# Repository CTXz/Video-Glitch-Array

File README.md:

# Video Glitch Array

Video Glitch Array is a glitch art project in which I attempt to create aesthetics explicitly by manipulating VGA signals in real time trough analog and digital circuits. In a way, Video Glitch Array has become a nice sandbox for me to test and further develop my recently acquired skills in the field of electronics engineering.

## Contents

- [Why VGA](#Why-VGA)
- [Brief summary of how VGA works](#Brief-summary-of-how-VGA-works)
- [Circuits](#Circuits)
- [Open Hardware](#Open-Hardware)
- [Credits](#Credits)
- [Demonstrations](#Demonstrations)

## Why VGA

Quite frankly, the initial reason why I chose to tamper with VGA signals over, say the much more common and within the analog glitch art community preferred composite video signals, is because that is simply what I had available at home. That being said, while VGA certainly has its drawbacks when it comes to glitch art, mostly due to the rather high frequencies of the color signals, it also comes with a variety of advantages.

While the VGA port has practically gone extinct from host peripherals, it is still very common to find a VGA port on most displays, including many released even at the time of writing. Yet I am not aware of many LCD displays and projectors that support composite video. While HDMI and DVI ports are equally common, if not even more common than VGA at this point (with HDMI becoming more and more of a dominant player), those are digital interfaces and as many could imagine, are more clunky and difficult to work with. Another big advantage that VGA offers over composite is the absence of region specific differences. The VGA signal protocol, although a little hidden from the common user, is well established and standardized by now. Oh, and did I mention that VGA comes with its own 5V supply bus which can be used to power your glitch circuits without an external power source?

I could likely be going on forever, but I believe I have already managed to demonstrate that VGA can be an attractive medium for glitch art.

## Brief summary of how VGA works

I could explain how VGA signals work, however due to my brutally honest laziness and lack of competence in explaining things, I will leave you with a few resources which in my opinion do a much better job of explaining VGA than me. Many of the resources below explain VGA as part of a guide to create your own VGA driver, so it is not expected, nor required, that everything is understood.

- [Go Board - VGA Introduction](https://www.nandland.com/goboard/vga-introduction-test-patterns.html) by nandland
- [VGA - the Rest of the Story](http://www.xess.com/blog/vga-the-rest-of-the-story/) by Dave Vandenbout
- [VGA Video Output](http://web.mit.edu/6.111/www/labkit/vga.shtml) by Natahn Ickes
- [LCD monitors: Clock/Pitch and Phase controls for analog-input](http://www.techmind.org/lcd/phasexplan.html) by William Andrew Steer
- [VGA ECE3534](https://drive.google.com/file/d/1oJ0iN84QY8XnXu3txFdtZf11J46l7f6y/view?usp=sharing) by Virginia Tech (Pardon the mirror, but I can no longer find the original source)
- [The world's worst video card?](https://www.youtube.com/watch?v=l7rce6IQDWs) An amazing two part guide by Ben Eater
- [SW6 VGA Audio](http://www.partyzant.com.pl/instrukcje/matrixy/SW6_VGA_Audio.pdf) by Extron(R) Electronics, which provides fairly standard impedance specifications

Further, check out this [Stack Overflow question](https://electronics.stackexchange.com/questions/221536/vga-driver-not-working) which answers why there is no output when you apply a constant color signal. This will save you a large headache and time!

## Circuits

Each circuit has its very own directory in which you can find all ki-cad files, gerbers, and sometimes even LTSpice simulations. Every directory also comes with its very own README where I attempt to explain how the circuit works, which parts to order, as well as demonstrate the results provided by the circuit.

All my circuits follow a specific revision system.

- Schematics: [MAJOR].[MINOR]
- PCBs: [SCHEMATIC MAJOR].[SCHEMATIC MINOR].[PCB]

Here is a list of my current circuits:

- [VGA Breakout](https://github.com/CTXz/Video-Glitch-Array/tree/master/VGABreakout/README.md)
- [Pixel Slasher](https://github.com/CTXz/Video-Glitch-Array/tree/master/PixelSlasher/README.md)

## Open Hardware

Being a large supporter of open source software and hardware, it should go without saying that all circuits within this repository are licensed by the [TAPR Open Hardware License v1.0](https://tapr.org/ohl.html).

In the simplest terms, shall you decide to alter this project yourself and release the result, this license demands you to publish all changes that you have done. Commercial use, including commercial distribution of the circuits for ones own profit, is perfectly allowed as long as you comply with the license.

The last thing I would want to see is somebody enhancing my work and not sharing his progress with others.

## Credits

I would primarily like to thank the [brmlab hackerspace](https://brmlab.cz/) in Prague which has been providing me with the necessary knowledge, components and equipment to realize my ideas. I have also been granted the amazing opportunity to represent a part of the hackerspace on numerous "maker" exhibitions.

I would also like to thank the ["Glitch Artist Collective" discord server](https://discord.gg/r6NnsXX) for the great support and feedback I have been getting for my work.

## Contact

If you have any questions, I am frequently active on the ["Glitch Artist Collective" discord server](https://discord.gg/r6NnsXX)'s Circuit Bending & Analog Hardware channel. Alternatively you can send an email to `ctx.xda@gmail.com` where I will gladly answer your question(s).

## Demonstrations

You can find many more demonstrations on my [Instagram account for glitch art](https://www.instagram.com/video.home.systems/) where I also frequently provide updates on this project.

Photo Credit: Elson Li

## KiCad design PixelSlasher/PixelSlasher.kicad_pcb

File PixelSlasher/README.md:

# VGA Pixel Slasher

> **NOTE: This board is still in its early stages and may contain errors or perform sub-optimally. It is subject to major changes in the future.**

*An assembled Pixel Slasher rev 1.0 board which is still missing the CV input and has a few quirky labeling errors*

The Video Glitch Array Pixel Slasher is a device which delivers some seriously interesting glitch artifacts by cutting off color signals that exceed a specific brightness.

## Showcase

Unprocessed Glitch piece from my tribute to the Hong Kong protests: [No longer fiction.](https://photos.google.com/share/AF1QipNMWo8JjrfbMHIHrRe-PMUqr3MeHh42Vb7SW4W4gQFQ75YLK24xf4YlDsXKXHZIRA?key=Mk9kSk1EZlRZaGN0d3NoUjJIX3BaeVkyb2oyOEZn)

Photography credit: Anthony Wallace

---

Just another glitched sad mac

---

Pixel slasher glitching webcam video output

## Operation

The Video Glitch Array Pixel Slasher operates by using LM393 comparators to pull down color signals as soon as they exceed a certain voltage threshold, or in other words, a brightness threshold. The voltage thresholds for each color signal can be either set using slide potentiometers, or a 0-0.7V CV signal. Switching between the potentiometers and the CV input is simply a matter of flipping a switch.

Due to the fact that the non-inverting comparator input is tied to the color signal which is also being pulled down by a generic BC337 NPN transistor driven by the LM393 comparator output, an oscillation occurs. This in combination with the rather slow response time of the LM393 induces "wavy" repeating patterns across areas that exceed the threshold voltage, which take shape according to what's projected on the display.

Since the device operates by pulling down the VGA color signals, the color signals are connected in parallel to VGA wire. Thus, to set up the pixel slasher, simply connect the 5V and GND pins to the 5V and GND pins of your VGA cable or breakout board, and connect the color signal inputs in parallel to the VGA color wires.

If you're using the [Video Glitch Array Breakout Board](../VGABreakout/), setting up the pixel slasher is just a matter of closing all switches, and connecting the breakout board outputs to the appropriate pixel slasher inputs.    

*First Pixel Slasher prototype board*

## Schematic

You can download the Schematic for the VGA Pixel Slasher [here](Docs/Schematic.pdf). Alternatively you can import this board into KiCad and browse the schematic there.

## PCB

*J2, J3 and J4 provide a CV input for each color signal*

### Files

All KiCad PCB files, as well as gerbers can be found in this directory. To order the PCB, simply grab the grab the gerbers from the `Gerbers` directory and send them to your preferred PCB manufacturer.

### Components

The following table provides a list of the necessary components along with links to some examples. It is highly recommended to do a little research yourself here. Chances are that your local hardware store might be selling some components a lot cheaper.  

|Component                |Ref|Quantity|Examples|Notes/Tips|
|-------------------------|---|--------|--------|----------|
|1x5 2.54mm Female Headers|J1|1       |https://www2.mouser.com/ProductDetail/Molex/90147-1105?qs=sGAEpiMZZMs%252BGHln7q6pm8uos17B4BQAKRARw53BRV0%3D |Should you already have larger 2.54mm Female headers lying around, you could easily cut those instead of buying new ones|
|1x1 2.54mm Female Header |J2, J3, J4|3       |Not available, must be cut|As 1x1 female headers aren't available commercially, they must be cut. Alternatively you can use male pin headers instead|
|4.7mm Spacing SPST or SPDT Slide Switch|SW1, SW2, SW3|3       |https://www.amazon.com/SS12D10-Straight-Spacing-SS12D10G5-Vertical/dp/B07SJPN2HM/ref=sr_1_1?keywords=4.7mm+spacing+slide+switch&qid=1569413333&s=gateway&sr=8-1 | Should these become too pricey, feel free to edit the PCB in KiCad to fit a different switch|   
|LM393 DIP-8|U1, U2|2|https://www.mouser.de/ProductDetail/Texas-Instruments/LM393P?qs=sGAEpiMZZMuayl%2FEk2kXcddlv8%252BlGbVFYZWyaRldvtc%3D |These will almost certainly be available for dirt cheap at your local hardware store. Any DIP8 version will do (LM393P, LM393NG, etc.). If you would like to reuse the LM393 chips later on, it may be desired to use DIP-8 sockets.|
|BC337 TO-92 (ideally straight lead)|Q1, Q2, Q3|3|https://www.mouser.de/ProductDetail/Taiwan-Semiconductor/BC337-40-A1?qs=sGAEpiMZZMshyDBzk1%2FWiwIK8FF8XsC1RNbmjp0kCPo%3D |These will almost certainly be available for dirt cheap at your local hardware store. Bent lead packages will require a little force to insert trough.|
|10k, 60mm length, 45mm travel, 9mm width, linear slide potentiometers|RV1, RV2, RV3|3|https://www.mouser.de/ProductDetail/Bourns/PTA4553-2010CIB103?qs=sGAEpiMZZMtC25l1F4XBU%252BN3R7ksrj06xuOmWpCZ94k%3D | |
|3.3k Resistors|R2, R4, R6|3|https://www.mouser.de/ProductDetail/Vishay-Beyschlag/MBB02070C8200FCT00?qs=LkqrmUh5PII6P3inXi6ZTw%3D%3D&vip=1&gclid=CjwKCAjwlovtBRBrEiwAG3XJ-xNsZWIVeUh_aOER6JCOpZIqBPNapCJ1sNui1su29KHtjrVvs_qh3RoCCVQQAvD_BwE | Since these are pull-up resistors, their resistances aren't critical. Thus any ordinary 1k to 10k resistor will do just fine as well.|
|51k resistors|R1, R3, R5|3|https://www.mouser.de/ProductDetail/Yageo/MFR-25FTE52-51K?qs=sGAEpiMZZMu61qfTUdNhG0IXHLFuiNnd2ZOrYz8UKLE%3D | These should be as precise as possible. A too low resistance will shorten the practical potentiometer range. A too high resistance will cause effects to still appear even at the highest resistance.|

### Soldering

When soldering, I recommend to begin with the resistors first, as those are the smallest components. Then proceed with the female headers and transistors. Then solder in the LM393 chips, and last but not least, the switches and the slide pots.

Soldering the transistors leads can be a little difficult due to the density of the pins. It's highly recommended to have soldering braid/wick at your hand. In future revisions it is planned to increase the size of the transistor footprints.

### License

The VGA Pixel Slasher is licensed under the TAPR Open Hardware License v1.0 (See https://www.tapr.org/ohl.html)

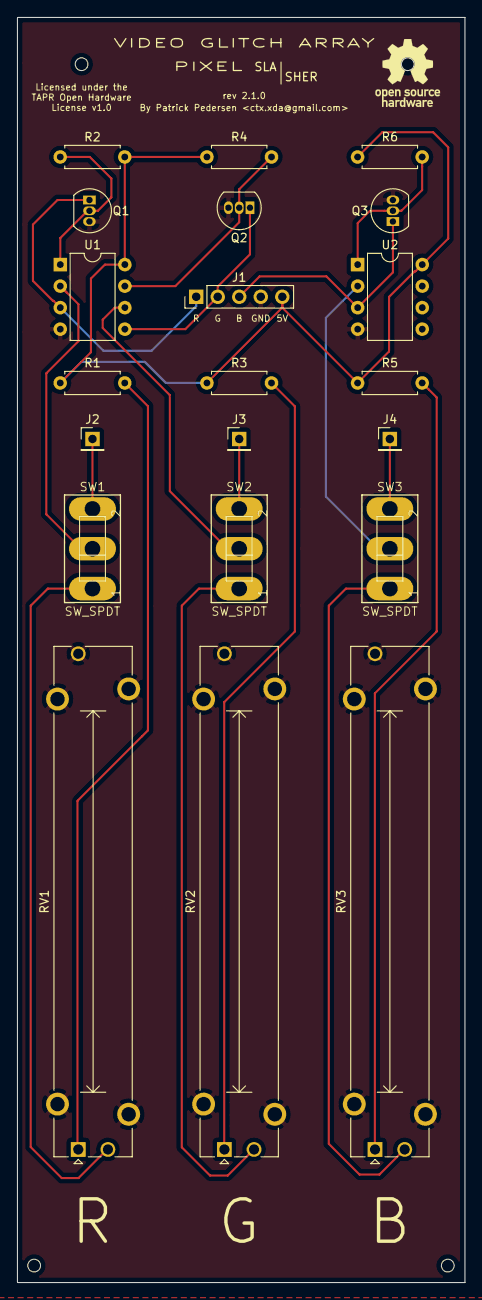
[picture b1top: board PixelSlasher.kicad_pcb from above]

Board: 2 copper layers, 52.8 x 149.3 mm, 21 parts (0 on the bottom side), 20 nets.

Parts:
J1: VGA Input; PinHeader_1x05_P2.54mm_Vertical
J2: CV Red; PinHeader_1x01_P2.54mm_Vertical
J3: CV Green; PinHeader_1x01_P2.54mm_Vertical
J4: CV Blue; PinHeader_1x01_P2.54mm_Vertical
Q1, Q2, Q3: BC337; TO-92_Inline
R1, R3, R5: 51k; R_Axial_DIN0207_L6.3mm_D2.5mm_P7.62mm_Horizontal
R2, R4, R6: 3.3k; R_Axial_DIN0207_L6.3mm_D2.5mm_P7.62mm_Horizontal
RV1, RV2, RV3: F4505N 10k; Potentiometer_Bourns_PTA4543_Single_Slide
SW1, SW2, SW3: SW_SPDT; 255SB
U1, U2: LM393; DIP-8_W7.62mm

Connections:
/VGA_5V_VCC_IN: J1.5, R1.1, R2.1, R3.1, R4.1, R5.1, R6.1, U1.8, U2.8
/VGA_B_IN: J1.3, Q3.1, U2.3
/VGA_G_IN: J1.2, Q2.1, U1.5
/VGA_R_IN: J1.1, Q1.1, U1.3
GND: J1.4, Q1.3, Q2.3, Q3.3, RV1.3, RV2.3, RV3.3, U1.4, U2.4
unnamed: J2.1, SW1.3
unnamed: J3.1, SW2.3
unnamed: J4.1, SW3.3
unnamed: Q1.2, R2.2, U1.1
unnamed: Q2.2, R4.2, U1.7
unnamed: Q3.2, R6.2, U2.1
unnamed: R1.2, RV1.1
unnamed: R3.2, RV2.1
unnamed: R5.2, RV3.1
unnamed: RV1.2, SW1.1
unnamed: RV2.2, SW2.1
unnamed: RV3.2, SW3.1
unnamed: SW1.2, U1.2
unnamed: SW2.2, U1.6
unnamed: SW3.2, U2.2

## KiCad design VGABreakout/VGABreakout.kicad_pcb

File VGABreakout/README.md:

# VGA Breakout

> **NOTE: This board is still in its early stages and may contain errors or perform sub-optimally. It is subject to major changes in the future.**

The Video Glitch Array Breakout board offers a clean and convenient replacement for messy generic VGA breakout boards. This board was developed out of the frequent frustration of having to deal with a rat's nest of cables and loose contacts.

In the upcoming future it is planned to add a amplifier section to the breakout board, to make interfacing with modular electronics easier.

## Operation

The VGA breakout board takes a incoming VGA signal on one side of the board and outputs an outgoing VGA signal on the other side of the board. At the moment, the orientation for plugging in the VGA cables is irrelevant, however this may change in the future with the addition of an amplifier. Only the relevant signals necessary for VGA glitching (R, G, B, HSYNC, VSYNC, 5V) are broken out. For each broken out signal/pin, with the exception of the 5V and ground pin, two ports are are provided, one at the input and one at the output.

Between the input and output, a SPST switch is present for every broken out signal. The operation of the input and output ports depends on the state of the SPST switch:

- When the switch is closed, the signal will pass trough. Devices connected on either of the two breakout ports will be connected in parallel.

- When the switch is opened, the signal can't pass trough. Devices connected across both breakout ports will be connected in series.

The 5V switch is there to increase the supply current on the 5V pin. It is highly recommended to initially keep the 5V switch closed as it may be required to power the monitors internal EEPROM that provides the host peripherals with generic information such as the display model, resolution etc. Once initialized, feel free to open the switch.

## Schematic

You can download the Schematic for the VGA Breakout board [here](Docs/Schematic.pdf). Alternatively you can import this board into KiCad and browse the schematic there.

## PCB

### Files

All KiCad PCB files, as well as gerbers can be found in this directory. To order the PCB, simply grab the grab the gerbers from the `Gerbers` directory and send them to your preferred PCB manufacturer.

### Components

> **NOTE: At the moment the D-SUB 15 footprints are wrong. The recommended D-SUB 15 connectors will not fit and thus require the anchor points to be cut and the pins to be bent!**

The following table provides a list of the necessary components for the breakout board, along with links to some examples. It is highly recommended to do a little research yourself here. Chances are that your local hardware store might be selling some components a lot cheaper.

|Component                |Ref|Quantity|Examples|Notes/Tips|
|-------------------------|---|--------|--------|----------|
|1x2 2.54mm Female Headers|J2 |1       |https://www2.mouser.com/ProductDetail/Molex/90147-1102?qs=sGAEpiMZZMs%252BGHln7q6pm8uos17B4BQAkcs7fV01%2F0k= |Should you already have larger 2.54mm Female headers lying around, you could easily cut those instead of buying new ones|
|1x5 2.54mm Female Headers|J3|1       |https://www2.mouser.com/ProductDetail/Molex/90147-1105?qs=sGAEpiMZZMs%252BGHln7q6pm8uos17B4BQAKRARw53BRV0%3D |Should you already have larger 2.54mm Female headers lying around, you could easily cut those instead of buying new ones|
|4.7mm Spacing SPST or SPDT Slide Switch|SW1, SW2, SW3, SW4, SW5, Sw6|5       |https://www.amazon.com/SS12D10-Straight-Spacing-SS12D10G5-Vertical/dp/B07SJPN2HM/ref=sr_1_1?keywords=4.7mm+spacing+slide+switch&qid=1569413333&s=gateway&sr=8-1 | Should these become too pricey, feel free to edit the PCB in KiCad to fit a different switch|   
|DS1038-15FBNSIA74 D-SUB 15 Connector|J1, J5|2|https://www.tme.eu/gb/details/dmr15f-hd/d-sub-connectors/connfly/ds1038-15fbnsia74/ | Should these become too pricey or are locally unavailable, feel free to edit the PCB in KiCad to fit a different D-SUB 15 connector|

### Soldering

When soldering, I highly recommend to begin with the female headers first, as those are the smallest components. Then proceed with the D-SUB connectors and finally the switches.

### License

The VGA Breakout Board is licensed under the TAPR Open Hardware License v1.0 (See https://www.tapr.org/ohl.html)

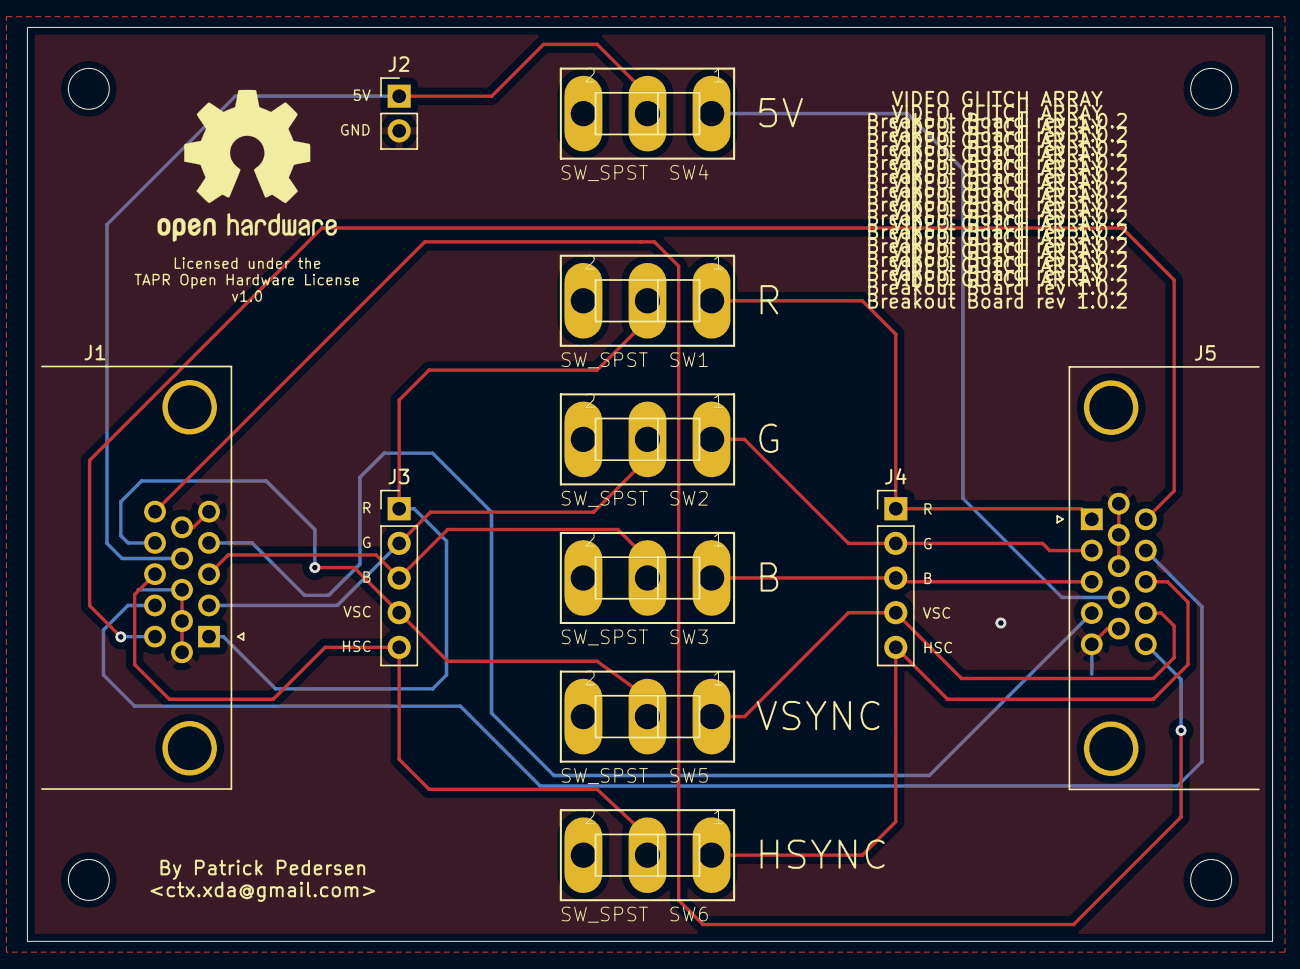
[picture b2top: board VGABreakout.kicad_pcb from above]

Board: 2 copper layers, 91.3 x 67.0 mm, 11 parts (0 on the bottom side), 17 nets.

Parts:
J1, J5: DB15_Female_HighDensity; DSUB-15-HD_Female_Horizontal_P2.29x1.98mm_EdgePinOffset8.35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
J2: Conn_01x02_Female; PinHeader_1x02_P2.54mm_Vertical
J3, J4: Conn_01x05_Female; PinHeader_1x05_P2.54mm_Vertical
SW1, SW2, SW3, SW4, SW5, SW6: SW_SPST; 255SB

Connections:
GND: J1.5, J1.6, J1.7, J1.8, J1.10, J2.2, J5.5, J5.6, J5.7, J5.8, J5.10
unnamed: J1.1, J3.1, SW1.1
unnamed: J1.2, J3.2, SW2.1
unnamed: J1.3, J3.3, SW3.1
unnamed: J1.4, J5.4
unnamed: J1.9, J2.1, SW4.1
unnamed: J1.11, J5.11
unnamed: J1.12, J5.12
unnamed: J1.13, J3.5, SW6.1
unnamed: J1.14, J3.4, SW5.1
unnamed: J1.15, J5.15
unnamed: J4.1, J5.1, SW1.2
unnamed: J4.2, J5.2, SW2.2
unnamed: J4.3, J5.3, SW3.2
unnamed: J4.4, J5.14, SW5.2
unnamed: J4.5, J5.13, SW6.2
unnamed: J5.9, SW4.2

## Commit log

2019-08-29 Added VGABreakout
2019-08-30 Added Pixel Slasher
2019-08-30 Pixel Slasher: Added LICENSE.txt
2019-08-30 Pixel Slasher: Added gerbers
2019-08-31 Added gitignore
2019-08-31 VGABreakout: rev1.1: Fixed text orientation and rotated board in pcbnew
2019-09-01 Pixel Slasher: Rev 1.1: Inverted direction of slide pots
    The previous configuration was counter-intuitive as we were decreasing
    the number of artifacts as the slider went up.
2019-09-02 Updated PCB revisioning system to <SCHEM MAJOR>.<SCHEM MINOR>.<PCB>
2019-09-02 Pixel Slasher: Added LTSpice model
2019-09-02 Added .log and .raw to .gitignore
2019-09-04 Added cache and autosave files to gitignore
2019-09-04 Pixel Slasher: Rev 2.0.0: Added option for CV input
2019-09-04 Pixel Slasher: rev 2.0.1: Re-oriented J1 to be more intuitive
2019-09-04 Pixel Slasher: Moved res refs and vals to the left
2019-09-04 PixelSlasher: Updated gerbers
2019-09-04 PixelSlasher: Rev 2.0.2: Set pin header labels to silk screen
2019-09-11 PixelSlasher: Rev 2.0.3: Fixed R2 ref designator + minor changes in distances for ref designators
2019-09-11 PixelSlasher: Rev 2.0.4: Vertically centered CV/Pot switches
2019-09-11 Added RULES.txt
2019-09-11 VGABreakout: Rev 1.0.2: Fixed lables and trace irregularities/asymetries
2019-09-18 Added a main README
2019-09-18 README: Added TOC + few minor changes
2019-09-18 Added images to repo
2019-09-25 VGA Breakout: Added README
2019-09-25 README: Reference images locally
2019-09-25 VGABreakout: README: Added details regarding the 5V switch
2019-09-25 VGABreakout: Minor changes
2019-09-25 PixelSlasher: Rev 2.0.5: Ground slide pot case mounts
2019-09-29 VGABreakout: README: Included pics of PCB and Schematic
2019-10-01 VGABreakout: README: Added notations
2019-10-01 README: Added "Go Board - VGA Introduction" to resources
2019-10-01 README: Fixed link for Ben Eater's "The world's worst video card?"
2019-10-13 PixelSlasher: 2.1.0: Updated values of R1, R3 and R5 to 51k
    Now we're making nearly full use of the slide pots
2019-10-13 VGABreakou: README: Correction
2019-10-13 PixelSlasher: Added documentation
2019-10-15 PixelSlasher: README: Fixed typo
2019-10-24 README: Why VGA: Updated
2020-02-09 VGABreakout & Pixelslasher: Added refs to parts list

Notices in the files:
PixelSlasher/PixelSlasher.kicad_pcb:
License: TAPR Open Hardware License v1.0
